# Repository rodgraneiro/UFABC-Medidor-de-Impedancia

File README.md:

# UFABC---Medidor-de-Impedancia

Comentário inserido por Olavo para testar o Visual Studio Code

### Exemplo de código
~~~
$ mkdir /home/olavo/github
$ cd /home/olavo/github
~~~

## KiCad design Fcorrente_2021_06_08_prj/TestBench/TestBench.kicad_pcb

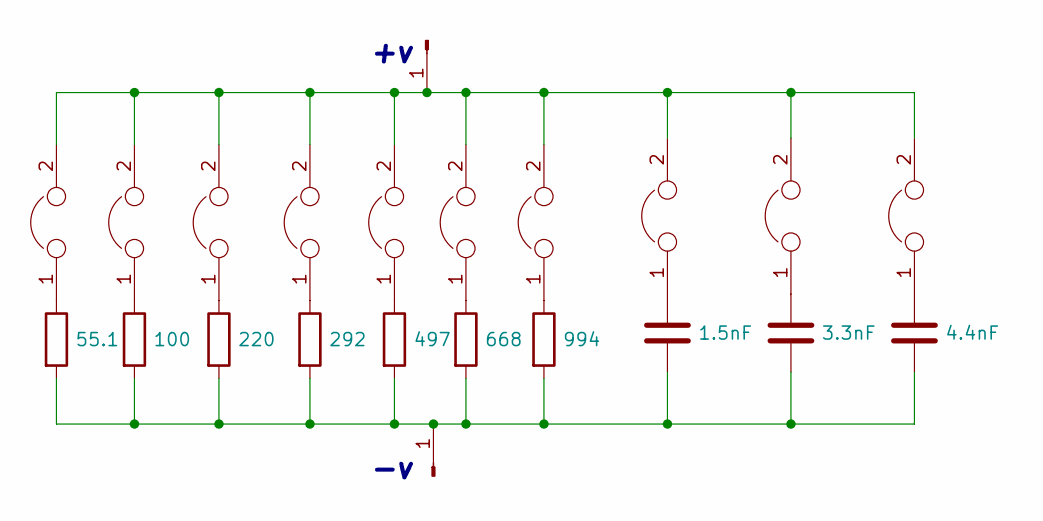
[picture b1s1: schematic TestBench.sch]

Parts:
C1: 1.5nF; C_Disc_D12.5mm_W5.0mm_P10.00mm
C2: 3.3nF; C_Disc_D12.5mm_W5.0mm_P10.00mm
C3: 4.4nF; C_Disc_D12.5mm_W5.0mm_P10.00mm
J1, J2: Conn_01x01_Male; PinHeader_1x01_P2.00mm_Vertical
JP1, JP2, JP3, JP4, JP5, JP6, JP7, JP8, JP9, JP10: Jumper; PinHeader_1x02_P2.00mm_Vertical
R1: 55.1; R_Axial_DIN0207_L6.3mm_D2.5mm_P15.24mm_Horizontal
R2: 100; R_Axial_DIN0207_L6.3mm_D2.5mm_P15.24mm_Horizontal
R3: 220; R_Axial_DIN0207_L6.3mm_D2.5mm_P15.24mm_Horizontal
R4: 292; R_Axial_DIN0207_L6.3mm_D2.5mm_P15.24mm_Horizontal
R5: 497; R_Axial_DIN0207_L6.3mm_D2.5mm_P15.24mm_Horizontal
R6: 668; R_Axial_DIN0207_L6.3mm_D2.5mm_P15.24mm_Horizontal
R7: 994; R_Axial_DIN0207_L6.3mm_D2.5mm_P15.24mm_Horizontal

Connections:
unnamed: C1.1, JP8.1
unnamed: C1.2, C2.2, C3.2, J2.1, R1.2, R2.2, R3.2, R4.2, R5.2, R6.2, R7.2
unnamed: C2.1, JP9.1
unnamed: C3.1, JP10.1
unnamed: J1.1, JP1.2, JP2.2, JP3.2, JP4.2, JP5.2, JP6.2, JP7.2, JP8.2, JP9.2, JP10.2
unnamed: JP1.1, R1.1
unnamed: JP2.1, R2.1
unnamed: JP3.1, R3.1
unnamed: JP4.1, R4.1
unnamed: JP5.1, R5.1
unnamed: JP6.1, R6.1
unnamed: JP7.1, R7.1

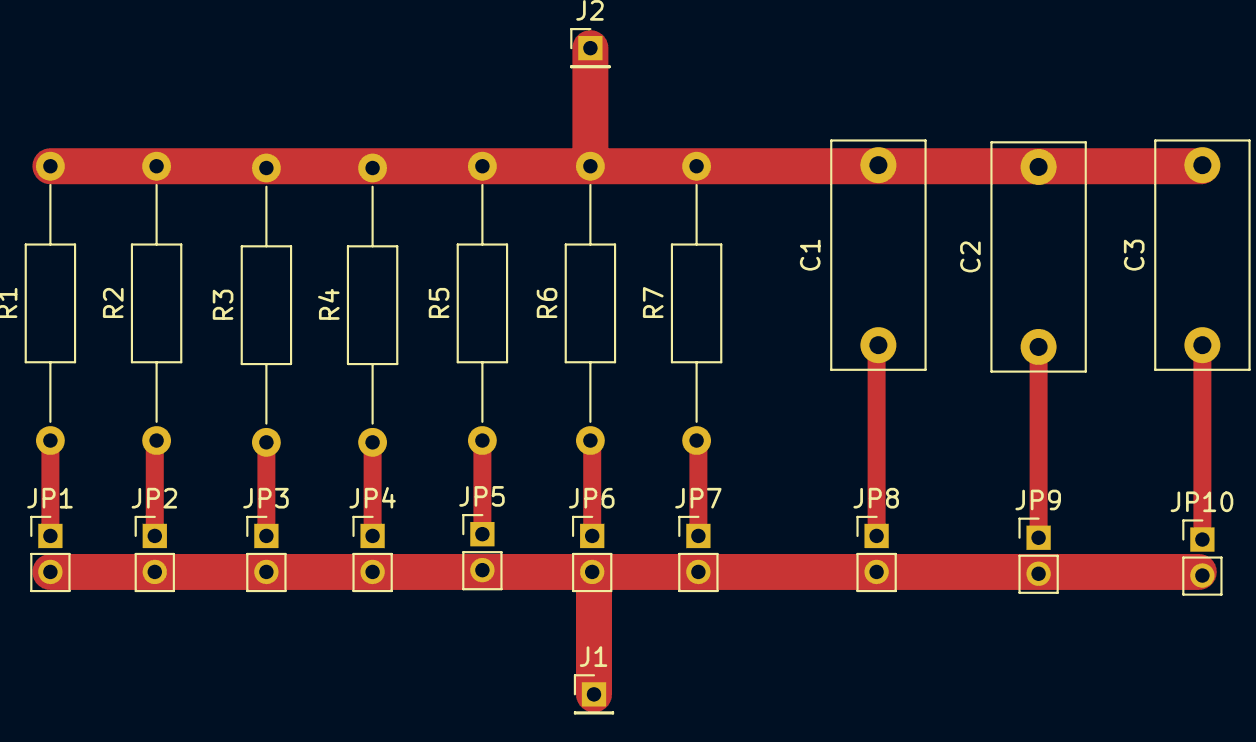
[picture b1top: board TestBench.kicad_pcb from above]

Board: 2 copper layers, 22 parts (0 on the bottom side), 12 nets.

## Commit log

2021-03-09 Arrumando identação da função setup().
2021-03-09 Alterando comentário.
2021-03-09 Incluindo canal Mestre
    Incluindo canal Mestre
2021-03-09 Teste de comentario do Olavo
2021-03-09 Exemplo de código no formato md
2021-03-11 adequação variaveis
2021-03-17 renomeando variáveis
2021-03-18 renomear variáveis
2021-03-23 revisão de variáveis
2021-03-23 debug nova versão
2021-03-26 debug canal mestre
2021-03-27 debug canalMestre 26mar2021
2021-03-28 debug canalMestre 27mar21
2021-03-29 debug ch Mestre 28mar21
2021-03-29 correção inteiro da fase
    Obs. a variável tipo "byte" só pode transmitir via I2C ângulos de até 255 graus.
2021-03-30 debug ch mestre e escravo
2021-04-04 alteração union float I2C
    Conversão de float para 4 bytes para transmissão I2C
2021-04-05 debug I2C
2021-04-06 debug I2C 05abr21
2021-04-07 remover lixo
2021-04-09 remover lixo 08abr21
2021-04-09 debug bit errático
2021-04-13 debug pto errático2
2021-04-13 remover lixo 12abd21
2021-04-18 debug error ptos 18abr21
2021-04-19 debug 625kHz
2021-04-19 Remove lixo
2021-04-21 piE 10ptos 125kHz SR 625kHz
2021-04-23 debug 625kHz 22abr21
2021-04-24 teste mil ptos1
2021-04-25 teste mil ptos
2021-05-03 processing
2021-05-04 medições pto erráticos
2021-05-11 graf_processing
2021-05-11 Arquivos - medição gráfico processing
2021-05-18 tst processing
2021-05-28 ajuste tempo
2021-06-01 med f corrente
2021-06-01 tst f corrente 1jun21
2021-06-08 cal FC
2021-07-20 calibracao
2021-09-29 Pastas
2021-09-30 Create Medição Rsentinela com terminais em curto-circuito
2021-09-30 Update Medição Rsentinela com terminais em curto-circuito
2021-09-30 Create Codigo LTSpice
2021-09-30 Update Codigo LTSpice
2021-09-30 trimpot
2021-10-01 Create Procedimento da medição
2021-10-01 Update Procedimento da medição
2021-10-01 Rename Procedimento da medição to Procedimento da medição.md
2021-10-01 sort
2021-10-02 GRAF
2021-10-02 outros
2021-10-04 Imp_FCorrente
2021-10-04 surf
2021-10-05 ltspice
2021-10-05 dadosMIE
2021-10-05 excl
2021-10-05 proc
2021-10-26 labL001
2021-10-26 L001
2022-01-11 arquivos
2022-01-11 Programas para estutar a calibracao.
2022-01-11 Adaptacao para Matlab
2022-01-12 correcao arquivo
2022-01-17 dadosArtigo
2022-01-18 med verificação
2022-02-22 DUEtrimado
2022-02-22 comentários
2022-02-22 medicoes
2022-02-22 Adicionando funcao para trimar os vetores.
2022-02-24 bqbq
2022-02-25 tst2
2022-02-25 transFunc
2022-02-26 converte p funcao
2022-02-27 coverte func
2022-03-01 converte funcao
2022-03-02 converte func 2fev22
2022-03-03 convert func 3mar22
2022-03-03 converte func 3mar22 1
2022-03-03 back up old files
2022-03-04 converte func CM 3mar22
2022-03-04 converte func CM 3mar22 1
2022-03-07 converte func 06mar22
2022-03-07 converte func 7mar22
2022-03-08 converte func 8mar22
2022-03-09 converte func 9mar22
2022-03-10 converte func 9mar22a
2022-03-10 converte func 9mar22b
2022-03-12 convert func 12mar22
2022-03-14 convert func
2022-03-15 conerte func 14mar22a
2022-03-15 converte func 15mar22
2022-11-27 save
